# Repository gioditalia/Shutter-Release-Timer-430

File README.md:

# Shutter Release Timer 430
Msp430g2231 Shutter Release Timer project

### Missing features
- [ ] add programming pins

### Future development
- [ ] improve time setting (using 5/6 bit for setting time?)
- [ ] replace LED with 7-segment display?

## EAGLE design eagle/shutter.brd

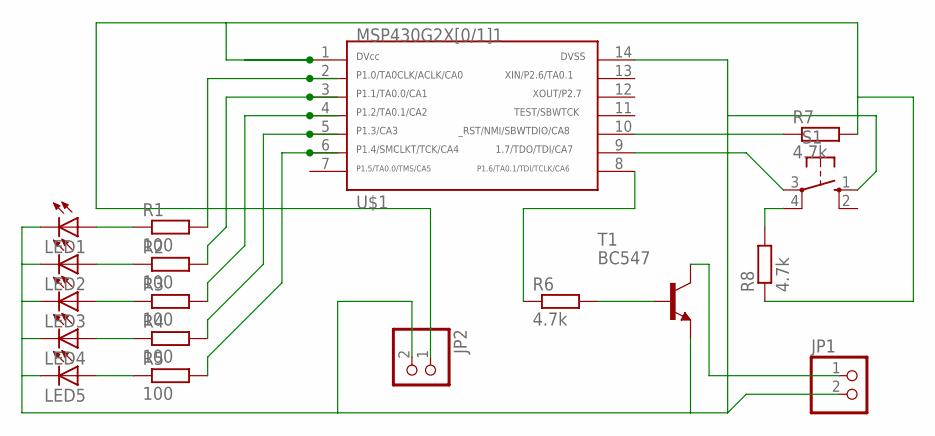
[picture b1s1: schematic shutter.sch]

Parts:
JP1, JP2: PINHD-1X2; 1X02
LED1, LED2, LED3, LED4, LED5: LED_ESML0603; LED_SML0603
R1, R2, R3, R4, R5: 100; R0603
R6, R7, R8: 4.7k; R0603
S1: 10-XX; B3F-10XX
T1: BC547; TO92
U$1: G2X[0/1]1---PW14; PW14

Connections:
GND: JP1.2, JP2.2, LED1.C, LED2.C, LED3.C, LED4.C, LED5.C, S1.1 (S), T1.1 (E), U$1.14
unnamed: R7.1, U$1.10
unnamed: JP2.1, R7.2, R8.1, U$1.1
unnamed: R6.2, T1.2 (B)
unnamed: LED1.A, R1.1
unnamed: LED2.A, R2.1
unnamed: LED3.A, R3.1
unnamed: LED4.A, R4.1
unnamed: LED5.A, R5.1
unnamed: R1.2, U$1.2
unnamed: R2.2, U$1.3
unnamed: R3.2, U$1.4
unnamed: R4.2, U$1.5
unnamed: R5.2, U$1.6
unnamed: R6.1, U$1.8
unnamed: S1.3, U$1.9
unnamed: R8.2, S1.4 (P1)
unnamed: JP1.1, T1.3 (C)

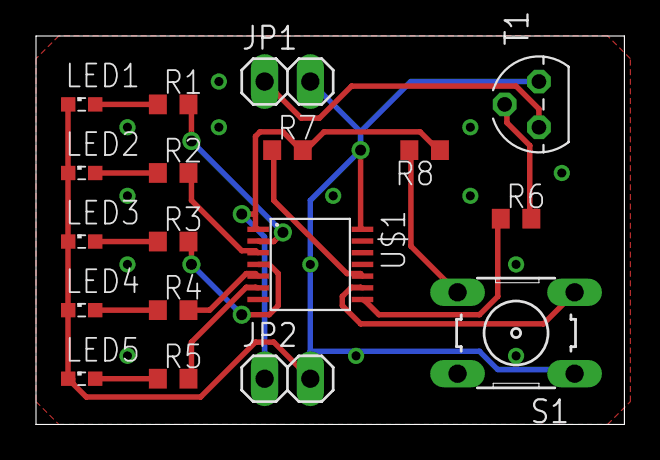
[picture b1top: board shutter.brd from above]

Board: 2 copper layers, 32.7 x 21.6 mm, 18 parts (0 on the bottom side), 18 nets.

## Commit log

2016-02-11 added comments
2016-02-24 Shutter-Release-Timer-430 eagle files
2016-02-24 fixed
2016-02-24 fixed - from 15 to 30 seconds on button interrupt
2016-02-25 fixed GND vias
